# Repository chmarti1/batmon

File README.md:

#BatMon

A battery monitor system using the LabJack U3 DAQ
---
## In this README
- About
- License
- Warnings

## About
This repository includes files for a PC board design, Bill-of-Materials (BOM), and code for monitoring a battery from a Linux computer.  These materials are intended for information and inspiration; they do not constitute a complete instruction set.

The designed system uses a U3 DAQ to perform analog measurements and a temperature -measurement.  A shunt resistor provides small (+/-0.1V) signal indicating current to and from the battery, and direct connection to the battery terminals provides a measurement of the battery voltage.

**Figure 1** A system overview

I designed this system on a 12V AGM SLA battery, but it can be applied on battery arrays of other chemistries as well.

## License
BatMon: A battery monitoring system using the LabJack U3.  
Copyright (c) 2021 Christopher R. Martin PhD

These materials are released under the [GNU GPLv3](https://www.gnu.org/licenses/gpl-3.0.en.html).  This program is free software: you can redistribute it and/or modify it under the terms of the GNU General Public License as published by the Free Software Foundation, either version 3 of the License, or (at your option) any later version.

This program is distributed in the hope that it will be useful, but WITHOUT ANY WARRANTY; without even the implied warranty of MERCHANTABILITY or FITNESS FOR A PARTICULAR PURPOSE.  See the GNU General Public License for more details.

You should have received a copy of the GNU General Public License along with this program.  If not, see https://www.gnu.org/licenses/gpl-3.0.en.html .

## Warnings
- Working with power electronics can be dangerous and should only be done by qualified individuals.
- Special care should be taken to avoid accidental short-circuits
- This work is shared without warranty or suitability for a specific purpose.  
- This work should not be used in systems where failure may cause injury, loss of life, or damage to property.
- The performance of the designs shared here depend on workmanship and the sufficient care taken during calibration and installation.
- For safety, all connections to the positive terminal of the battery should be fused to limit the flow of current.

## Circuit

The circuit design is shown in [circuit.pdf](./images/circuit.pdf), and the PC board layout is shown below.  The DB-15 connector on the right-hand side connects to the LabJack U3 DB-15 connection.  There are four screw terminals on the left-hand side that permit the shunt and terminal measurements.  All inputs are reverse polarity and over-voltage tolerant up to 50V.

There are five low-current indicator LEDs (two red and three green).  The first red LED is tied to a special ALARM circuit, which also fires a buzzer.  The buzzer can be switched off manually by a toggle switch mounted at SW1 (every buzzer needs an off switch).

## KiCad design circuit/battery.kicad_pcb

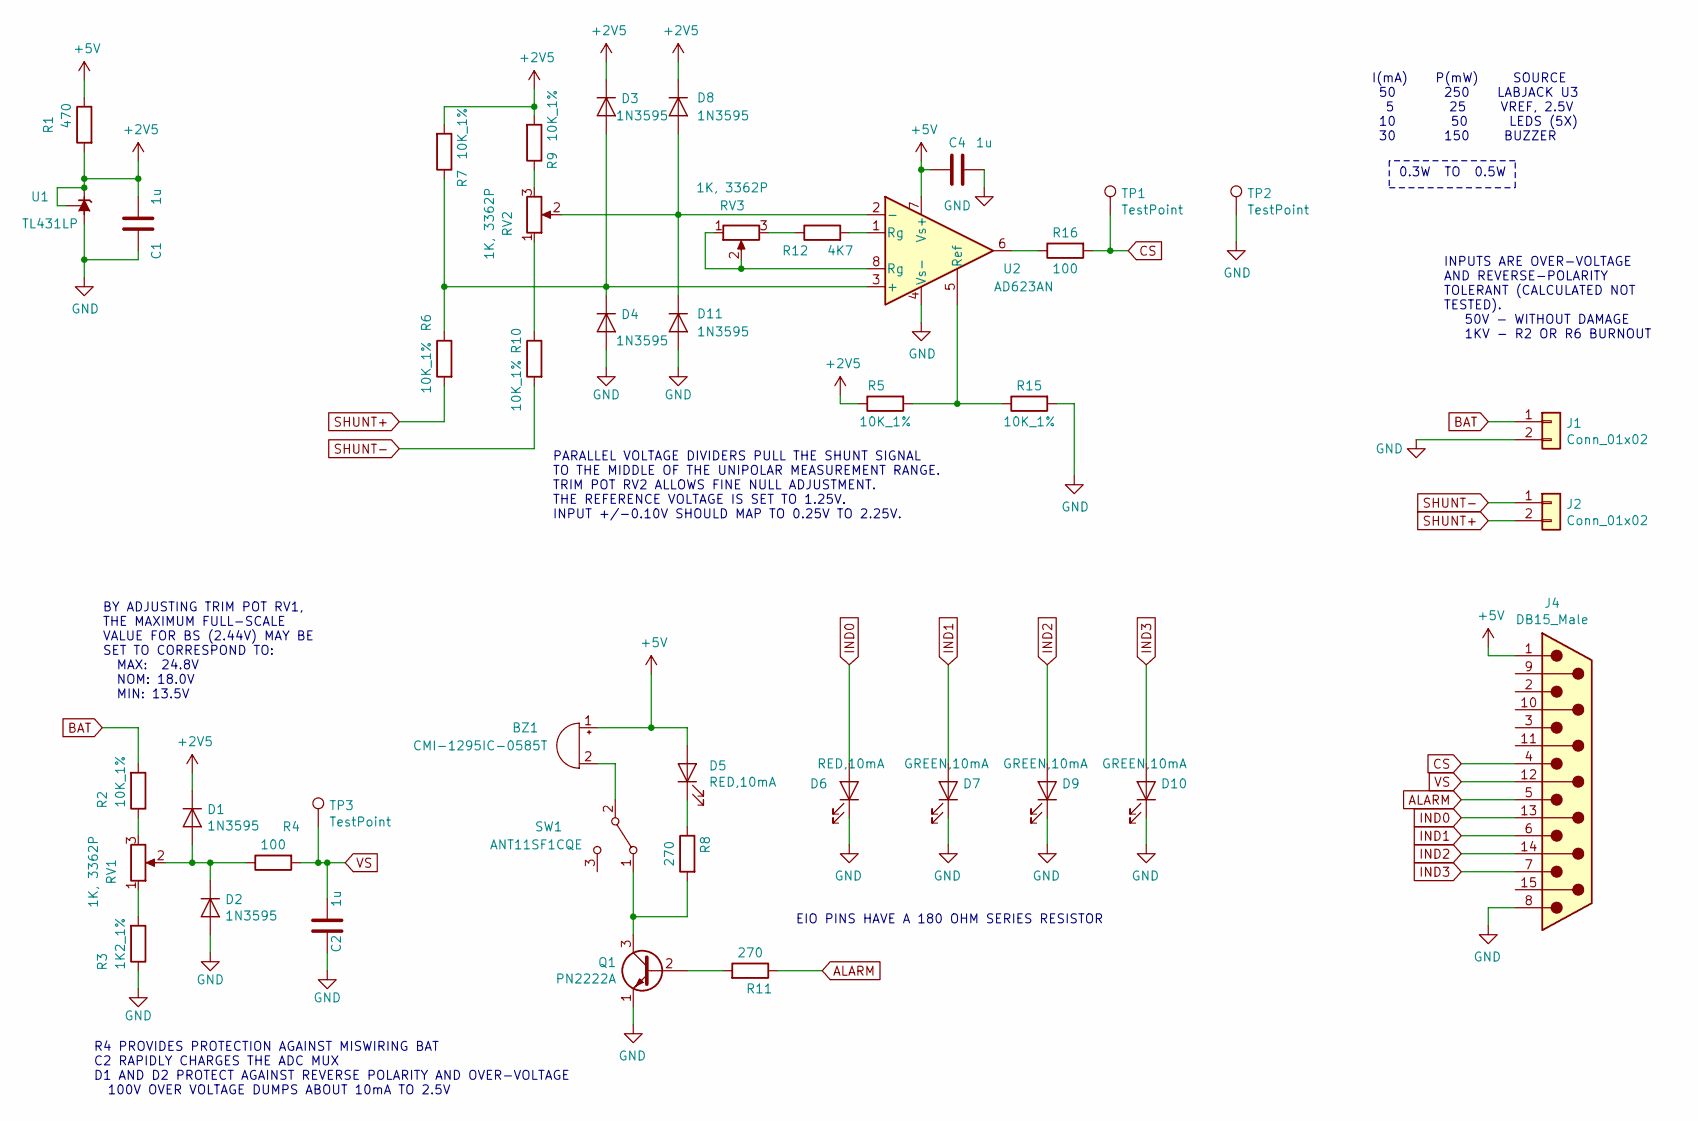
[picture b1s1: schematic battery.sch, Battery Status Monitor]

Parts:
BZ1: CMI-1295IC-0585T; Buzzer_12x9.5RM7.6
C1, C2, C4: 1u; C_Disc_D3.0mm_W1.6mm_P2.50mm
D1, D2, D3, D4, D8, D11: 1N3595; D_DO-35_SOD27_P7.62mm_Horizontal
D5, D6: RED,10mA; LED_D5.0mm
D7, D9, D10: GREEN,10mA; LED_D5.0mm
J1, J2: Conn_01x02; TerminalBlock_Phoenix_MKDS-1,5-2-5.08_1x02_P5.08mm_Horizont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
J4: DB15_Male; DSUB-15_Male_Horizontal_P2.77x2.84mm_EdgePinOffset7.70mm_Ho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
Q1: PN2222A; TO-92_Inline_Wide
R1: 470; R_Axial_DIN0207_L6.3mm_D2.5mm_P10.16mm_Horizontal
R2, R5, R6, R7, R9, R10, R15: 10K_1%; R_Axial_DIN0207_L6.3mm_D2.5mm_P10.16mm_Horizontal
R3: 1K2_1%; R_Axial_DIN0207_L6.3mm_D2.5mm_P10.16mm_Horizontal
R4, R16: 100; R_Axial_DIN0207_L6.3mm_D2.5mm_P10.16mm_Horizontal
R8, R11: 270; R_Axial_DIN0207_L6.3mm_D2.5mm_P10.16mm_Horizontal
R12: 4K7; R_Axial_DIN0207_L6.3mm_D2.5mm_P10.16mm_Horizontal
RV1, RV2, RV3: 1K, 3362P; Potentiometer_Bourns_3296W_Vertical
SW1: ANT11SF1CQE; SW_CIT_ANT_SPDT
TP1, TP2, TP3: TestPoint; TestPoint_Loop_D2.60mm_Drill1.6mm_Beaded
U1: TL431LP; TO-92_Inline_Wide
U2: AD623AN; DIP-8_W7.62mm_LongPads

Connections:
+2V5: C1.1, D1.1 (K), D3.1 (K), D8.1 (K), R1.2, R5.1, R7.2, R9.2, U1.1 (REF), U1.3 (K)
+5V: BZ1.1 (-), C4.2, D5.2 (A), J4.1, R1.1, U2.7 (Vs+); also elsewhere on the board
ALARM: J4.5, R11.1
BAT: J1.1, R2.2
CS: J4.4, R16.2, TP1.1
GND: C1.2, C2.1, C4.1, D2.2 (A), D4.2 (A), D6.1 (K), D7.1 (K), D9.1 (K), D10.1 (K), D11.2 (A), J1.2, J4.8, Q1.1 (E), R3.1, R15.2, TP2.1, U1.2 (A), U2.4 (Vs-)
IND0: D6.2 (A), J4.13
IND1: D7.2 (A), J4.6
IND2: D9.2 (A), J4.14
IND3: D10.2 (A), J4.7
unnamed: BZ1.2 (+), SW1.2 (B)
unnamed: D1.2 (A), D2.1 (K), R4.1, RV1.2
unnamed: D3.2 (A), D4.1 (K), R6.1, R7.1, U2.3 (+)
unnamed: D5.1 (K), R8.1
unnamed: D8.2 (A), D11.1 (K), RV2.2, U2.2 (-)
unnamed: Q1.2 (B), R11.2
unnamed: Q1.3 (C), R8.2, SW1.1 (A)
unnamed: R2.1, RV1.3
unnamed: R3.2, RV1.1
unnamed: R9.1, RV2.3
unnamed: R10.1, RV2.1
unnamed: R12.1, RV3.3
unnamed: R12.2, U2.1 (Rg)
unnamed: R5.2, R15.1, U2.5 (Ref)
unnamed: R16.1, U2.6
unnamed: RV3.1, RV3.2, U2.8 (Rg)
SHUNT+: J2.2, R6.2
SHUNT-: J2.1, R10.2
VS: C2.2, J4.12, R4.2, TP3.1

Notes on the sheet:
BY ADJUSTING TRIM POT RV1, THE MAXIMUM FULL-SCALE VALUE FOR BS (2.44V) MAY BE SET TO CORRESPOND TO: MAX: 24.8V NOM: 18.0V MIN: 13.5V
R4 PROVIDES PROTECTION AGAINST MISWIRING BAT C2 RAPIDLY CHARGES THE ADC MUX D1 AND D2 PROTECT AGAINST REVERSE POLARITY AND OVER-VOLTAGE 100V OVER VOLTAGE DUMPS ABOUT 10mA TO 2.5V
PARALLEL VOLTAGE DIVIDERS PULL THE SHUNT SIGNAL TO THE MIDDLE OF THE UNIPOLAR MEASUREMENT RANGE. TRIM POT RV2 ALLOWS FINE NULL ADJUSTMENT. THE REFERENCE VOLTAGE IS SET TO 1.25V. INPUT +/-0.10V SHOULD MAP TO 0.25V TO 2.25V.
EIO PINS HAVE A 180 OHM SERIES RESISTOR
I(mA) P(mW) SOURCE 50 250 LABJACK U3 5 25 VREF, 2.5V 10 50 LEDS (5X) 30 150 BUZZER
0.3W TO 0.5W
INPUTS ARE OVER-VOLTAGE AND REVERSE-POLARITY TOLERANT (CALCULATED NOT TESTED). 50V - WITHOUT DAMAGE 1KV - R2 OR R6 BURNOUT

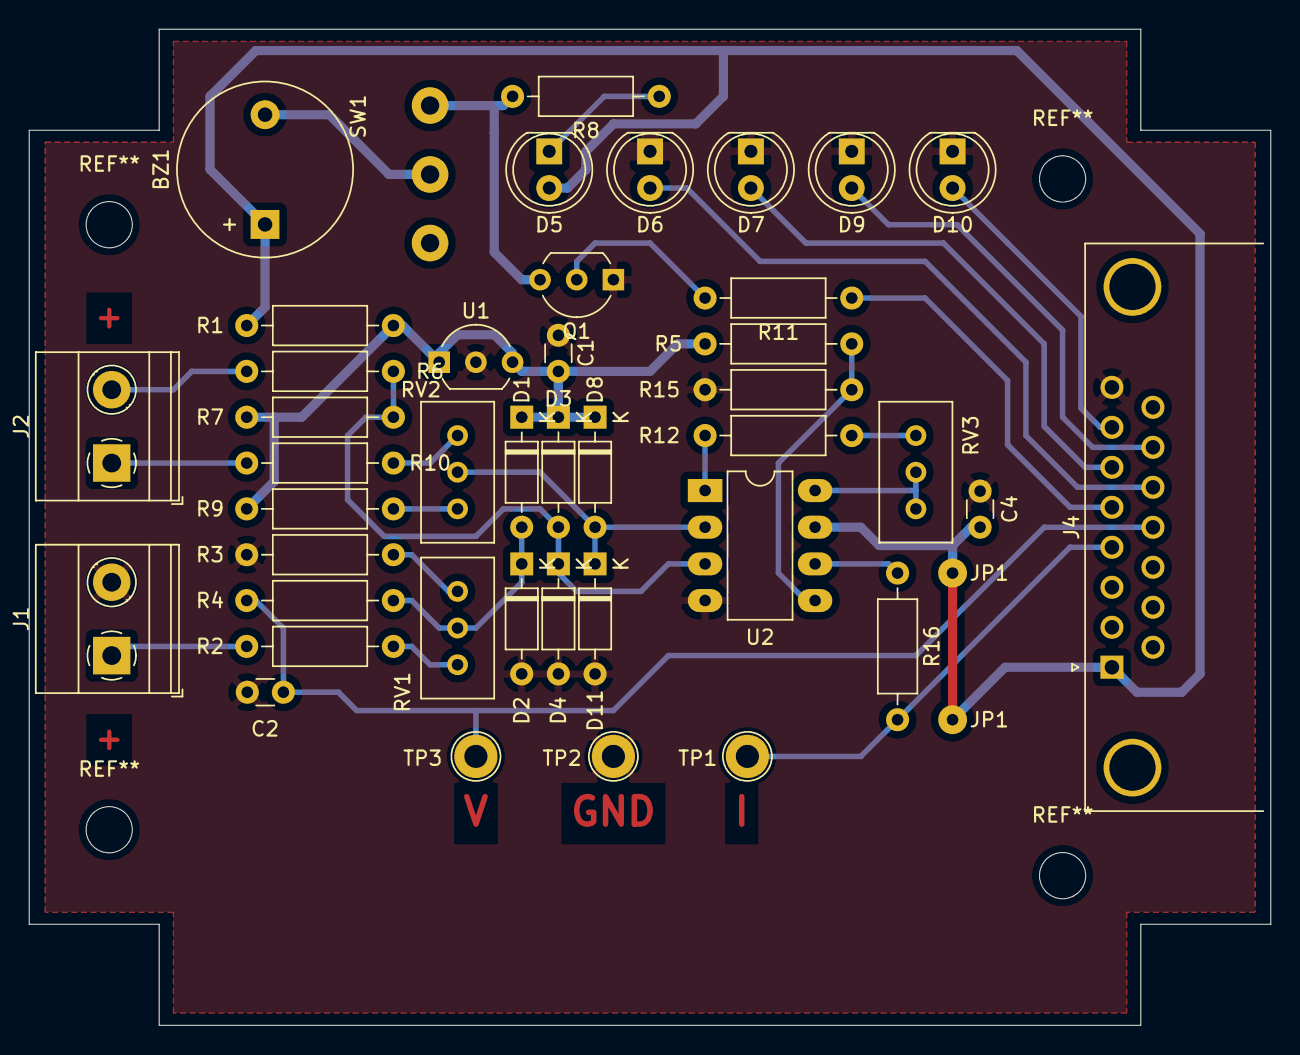
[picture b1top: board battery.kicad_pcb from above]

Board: 2 copper layers, 86.0 x 69.0 mm, 44 parts (0 on the bottom side), 29 nets.

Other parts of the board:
JP1, JP1#2: SolderWirePad_1x01_Drill0.8mm

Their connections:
+5V: JP1.1, JP1#2.1; also elsewhere on the board

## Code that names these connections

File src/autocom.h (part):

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/* ACINIT - Initialize the U3
 *  Configures the U3 for use with the battery monitor system once the
 * connection is already open. The process is:
 *  (1) Configures ALARM and IND0-IND3 pins for output and 
 *      sets all High while setting the U3 LED off
 *  (2) Sets ALARM and IND0-IND3 Low and turns the U3 LED on.
 * If there is an error in the initialization phase and it cannot 
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
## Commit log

2021-12-04 Final board design; production complete
2021-12-04 Placed digikey order
2021-12-06 Started writing documentation
2021-12-07 Demonstrated communication and acinit.
2021-12-07 Finished adding functionality to acinit(). Testing next.
2021-12-09 Started constructing the configuration system.
2021-12-09 Shifted to a multi-output error messaging system
2021-12-12 Bug; acinit fails
2021-12-12 Fixed bug: xmit(handle.. -> xmit(dev...
2021-12-13 Demonstrated bmcmd with indicator and alarm commands
2021-12-15 Demonstrated streaming
2021-12-30 started adding documentation to bmcmd
2022-02-18 Changed file handling to be by path instead of fd, drafted early test of batmon
2022-09-11 Rewrite of EVERYTHING for 60Hz cycle averaging
2022-09-15 Finally debugged streaming. Deveoping new chargemodel interface
2022-10-25 Progress writing the service - still need new stat and data logging
2022-10-25 Added acdata to autocom
2022-10-25 Prototype code ready for implementation
2022-10-25 Demonstrated working bmsvc.bin
2022-10-26 Cleaned up debug code, fixed stream_start xmit omission? added stat file support
2022-11-12 Fully implemented - added 10,000 entry data file threshold before being cleared
2023-05-07 Added a step to check for an excessively large log file - not yet tested
